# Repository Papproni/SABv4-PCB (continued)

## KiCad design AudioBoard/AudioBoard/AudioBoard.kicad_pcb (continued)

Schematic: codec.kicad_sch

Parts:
C57, C79: 100nF; C_0603_1608Metric; JLCPCB C14663
C58: 100uF tantal; CP_EIA-3528-21_Kemet-B; JLCPCB C16133
C67: 33nF; C_0805_2012Metric_Pad1.18x1.45mm_HandSolder; JLCPCB C21117
C68, C228: 1nF; C_0603_1608Metric; JLCPCB C1588
C80: 10uF tantal; CP_EIA-3216-18_Kemet-A; JLCPCB C7171
R45: 3k; R_0603_1608Metric; JLCPCB C4211
U1: LQFP-64_10x10mm_P0.5mm; JLCPCB C2913556

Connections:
+3.3V: U1.14 (PD/RST)
/HeadphoneAmplifier1/IN_N: U1.13 (OR4N); also elsewhere on the board
/HeadphoneAmplifier1/IN_P: U1.12 (OR4P); also elsewhere on the board
/HeadphoneAmplifier/IN_N: U1.11 (OL4N); also elsewhere on the board
/HeadphoneAmplifier/IN_P: U1.10 (OL4P); also elsewhere on the board
/Instrument_Input/OUT_N: U1.54 (ADC1LN); also elsewhere on the board
/Instrument_Input/OUT_P: U1.53 (ADC1LP); also elsewhere on the board
/Instrument_L1_return/OUT_N: U1.58 (ADC2LN); also elsewhere on the board
/Instrument_L1_return/OUT_P: U1.57 (ADC2LP); also elsewhere on the board
/Instrument_L1_send/IN_N: U1.40 (OL2P); also elsewhere on the board
/Instrument_L1_send/IN_P: U1.41 (OL2N); also elsewhere on the board
/Instrument_L2_return/OUT_N: U1.60 (ADC2RN); also elsewhere on the board
/Instrument_L2_return/OUT_P: U1.59 (ADC2RP); also elsewhere on the board
/Instrument_L2_send/IN_N: U1.42 (OR2P); also elsewhere on the board
/Instrument_L2_send/IN_P: U1.43 (OR2N); also elsewhere on the board
/Instrument_output_L/IN_N: U1.36 (OL1P); also elsewhere on the board
/Instrument_output_L/IN_P: U1.37 (OL1N); also elsewhere on the board
/Instrument_output_R/IN_N: U1.38 (OR1P); also elsewhere on the board
/Instrument_output_R/IN_P: U1.39 (OR1N); also elsewhere on the board
/MIC_preamp/OUT_N: U1.56 (ADC1RN); also elsewhere on the board
/MIC_preamp/OUT_P: U1.55 (ADC1RP); also elsewhere on the board
/XLR_output_L/IN_N_N: U1.9 (OR3N); also elsewhere on the board
/XLR_output_L/IN_N_P: U1.8 (OR3P); also elsewhere on the board
/XLR_output_R/IN_N_N: U1.7 (OL3N); also elsewhere on the board
/XLR_output_R/IN_N_P: U1.6 (OL3P); also elsewhere on the board
/codec/I2S.CLK: U1.21 (DBCLK), U1.28 (ABCLK)
/codec/I2S.SDI: U1.27 (ASDATA1)
/codec/I2S.SDO: U1.20 (DSDATA1)
/codec/I2S.WS: U1.22 (DLRCLK), U1.29 (ALRCLK)
/codec/SPI.CLK: U1.34 (CCLK)
/codec/SPI.CS: U1.35 (CLATCH)
/codec/SPI.MISO: U1.31 (COUT)
/codec/SPI.MOSI: U1.30 (CIN)
AD1939_FILTR: C79.2, C80.1, U1.47 (FILTR)
AD1939_LF: C67.2, C68.2, C228.2, U1.61 (LF)
AD1939_MCLKI: U1.2 (MCLKI/XI)
AD1939_MCLKO: U1.3 (MCLKO/XO)
AVDD: C68.1, C228.1, R45.2, U1.5 (AVDD), U1.45 (AVDD), U1.51 (AVDD), U1.62 (AVDD); also elsewhere on the board
DVDD: U1.17 (DVDD), U1.32 (DVDD); also elsewhere on the board
GND: C57.1, C58.2, C79.1, C80.2, U1.1 (AGND), U1.4 (AGND), U1.16 (DGND), U1.23 (VSUPPLY), U1.24 (VSENSE), U1.25 (VDRIVE), U1.33 (DGND), U1.44 (AGND), U1.46 (AGND), U1.48 (AGND); also elsewhere on the board
unnamed: C67.1, R45.1
VBIAS: C57.2, C58.1, U1.52 (CM); also elsewhere on the board

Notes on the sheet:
CM pin filter (can be used for BIAS)
FILTR filtering
MCLK is powered from external quarc osc
PLL Filters

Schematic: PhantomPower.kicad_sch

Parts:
SW2: SW_SPDT_321; SS-12D28G7; jlcpcbpart C2884748

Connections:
/power/PhantomPower/PP_EN_I: SW2.1 (C)
GND: SW2.3 (A); also elsewhere on the board
Phantom_PWR: SW2.2 (B); also elsewhere on the board

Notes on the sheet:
Must Do: - 10mA current limiter - Voltage of 24 or 48 Low noise

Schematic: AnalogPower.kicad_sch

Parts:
C88, C89, C97, C98: 100n; C_0402_1005Metric; JLCPCB C1591
C90: 33nF; C_0805_2012Metric_Pad1.18x1.45mm_HandSolder; JLCPCB C21117
C91, C92, C93, C94, C95, C96, C106, C140: 10uF; C_0402_1005Metric; JLCPCB C440198
C103, C104, C105, C107, C138, C139: 100uF; CP_Elec_5x5.4; JLCPCB C48970701
FL1, FL2: ACT3225R510-W2; L_CommonModeChoke_Coilank_ACM3225; JLCPCB C49420293
R1: 39k; R_0603_1608Metric; JLCPCB C23153
R2: 51k; R_0603_1608Metric; JLCPCB C23196
R3: 100k; R_0402_1005Metric; JLCPCB C25741
R7, R25: 10k; R_0603_1608Metric; JLCPCB C4184
R27, R34, R35, R43: 0R; R_0603_1608Metric_Pad0.98x0.95mm_HandSolder; JLCPCB C21189; not fitted
U21: TPS7A39; Texas_S-PVSON-N10_ThermalVias; JLCPCB C2685819
U22: URA2415S-6WR3; Converter_DCDC_TRACO_TEC2-12xxWI_24xxWI_48xxWI_THT; JLCPCB C21714378

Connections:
/power/AnalogPower/+15V: FL1.1, R34.1, U22.6 (+Vout)
/power/AnalogPower/+15V_FLT: C95.2, C96.2, C98.2, FL1.2, R34.2, U21.1 (INP), U21.2 (EN)
/power/AnalogPower/-15V: FL1.4, R27.1, U22.8 (-Vout)
/power/AnalogPower/-15V_FLT: C93.2, C94.2, C97.2, FL1.3, R27.2, U21.5 (INN)
/power/AnalogPower/EN: U22.3 (OnOff); also elsewhere on the board
/power/AnalogPower/VIN: C103.1, C104.1, C105.1, C106.2, FL2.1, R35.1; also elsewhere on the board
/power/AnalogPower/VIN_FLT_PMIN: C107.1, C138.1, C139.1, C140.2, FL2.2, R35.2, U22.2 (+Vin)
GND: C90.2, C91.1, C92.1, C93.1, C94.1, C95.1, C96.1, C97.1, C98.1, R7.2, U21.4 (GND), U21.11 (GND), U22.7 (Common); also elsewhere on the board
GNDPWR: C103.2, C104.2, C105.2, C106.1, FL2.4, R43.1; also elsewhere on the board
unnamed: R1.2, R2.1
unnamed: R25.1, U21.8 (BUF)
unnamed: C89.2, R3.1, R25.2, U21.7 (FBN)
unnamed: C88.1, R2.2, R7.1, U21.9 (FBP)
unnamed: C90.1, U21.3 (NR/SS)
unnamed: C107.2, C138.2, C139.2, C140.1, FL2.3, R43.2, U22.1 (-Vin)
VDD: C88.2, C91.2, R1.1, U21.10 (OUTP); also elsewhere on the board
VSS: C89.1, C92.2, R3.2, U21.6 (OUTN); also elsewhere on the board

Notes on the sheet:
Note: Filter can be bypassed if oscilaltions are visible

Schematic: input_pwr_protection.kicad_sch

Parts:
C56: 1uF; C_0603_1608Metric; JLCPCB C15849
C61: 2200uF; C_Radial_D16.0mm_H25.0mm_P7.50mm; lcscpart C2763
C141: 4.7uF; C_1206_3216Metric; JLCPCB C29823
R47: 5.6k; R_0603_1608Metric; JLCPCB C23189
R48: 30k; R_0805_2012Metric; JLCPCB C17621
R49: 100k; R_0402_1005Metric; JLCPCB C25741
R50: 20k; R_0603_1608Metric; JLCPCB C4184
R51: 0R; R_0603_1608Metric_Pad0.98x0.95mm_HandSolder; JLCPCB C21189; not fitted
R55: 0R; R_0603_1608Metric_Pad0.98x0.95mm_HandSolder; JLCPCB C21189
U3: TPS26600PWP; HTSSOP-16-1EP_4.4x5mm_P0.65mm_EP3.4x5mm_Mask2.66x2.46mm_The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; JLCPCB C544399

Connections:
/power/AnalogPower/EN: R55.2; also elsewhere on the board
/power/AnalogPower/VIN: C61.1, R49.1, R51.2, U3.15 (OUT), U3.16 (OUT); also elsewhere on the board
/power/input_pwr_protection/VIN: C56.1, R51.1, U3.1 (IN), U3.2 (IN); also elsewhere on the board
/power/input_pwr_protection/\SHDN: U3.7 (~SHDN); also elsewhere on the board
GNDPWR: C56.2, C61.2, R50.2, U3.9 (GND); also elsewhere on the board
unnamed: R47.1, U3.11 (ILIM)
unnamed: R48.1, U3.10 (IMON)
unnamed: C141.2, R47.2, R48.2, U3.3 (UVLO), U3.5 (OVP), U3.6 (MODE), U3.8 (RTN), U3.17 (RTN)
unnamed: C141.1, U3.12 (dVdT)
unnamed: R49.2, R50.1, R55.1, U3.14 (~FLT)

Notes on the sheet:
Vmonmax = 5V Rmon = Vmonmax / ( Ilim * 75*10e-6 ) Rmon = 30k Ilim = 12/Rilim = 2.14A Startup time = 1s EQ2: Tstartup/8000/VIN = Cdvdt_ideal = 5.2uF Cdvdt_real = 4.7uF
Chip Bypass
\SHDN ON: >1V OFF: 0V
PGD > 2V! for DCDC modules OpenDrain VIN=15V PGD = 2.5 V VIN=30V PGD = 5 V
RTN = UVLO = OVP 15V < VIN < 33V

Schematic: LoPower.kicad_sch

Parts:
C62, C85, C99: 100n; C_0402_1005Metric; JLCPCB C1591
C81, C86: 10uF tantal; CP_EIA-3216-18_Kemet-A; JLCPCB C7171
C82, C83, C84, C87: 47u; CP_Radial_D6.3mm_P2.50mm; JLCPCB C45673
C100: 10uF; C_0402_1005Metric; JLCPCB C440198
C101: 2200uF; C_Radial_D16.0mm_H25.0mm_P7.50mm; lcscpart C2763
C142, C143: 100uF; CP_Elec_5x5.4; JLCPCB C48970701
FB1: GZ2012D601TF; R_0805_2012Metric; JLCPCB C1017
FB2, FB3: BLM18PG121SN1D; Fuse_0603_1608Metric; JLCPCB C14709
U12, U13: AMS1117-3.3; SOT-223-3_TabPin2; JLCPCB C6186
U24: TURB2405YMD-30WR3; Converter_DCDC_TRACO_THL30-xxxxWI_THT; LCSC Part C5441767

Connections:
+5V: C85.2, C86.1, C101.1, FB1.1, FB3.2, U13.3 (VI); also elsewhere on the board
/power/AnalogPower/EN: U24.6 (Remote); also elsewhere on the board
/power/AnalogPower/VIN: FB2.1; also elsewhere on the board
AVDD: C82.1, C83.1, C84.1, U12.2 (VO); also elsewhere on the board
DVDD: C87.1, U13.2 (VO); also elsewhere on the board
GND: C62.1, C81.2, C82.2, C83.2, C84.2, C85.1, C86.2, C87.2, C99.1, C100.1, C101.2, U12.1 (GND), U13.1 (GND), U24.5 (-Vout); also elsewhere on the board
GNDPWR: C142.2, C143.2, U24.2 (-Vin); also elsewhere on the board
unnamed: C62.2, C81.1, FB1.2, U12.3 (VI)
unnamed: C142.1, C143.1, FB2.2, U24.1 (+Vin)
unnamed: C99.2, C100.2, FB3.1, U24.3 (+Vout)

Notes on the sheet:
Convert +18-24V

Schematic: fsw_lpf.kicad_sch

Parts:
C149: 100n; C_0402_1005Metric; JLCPCB C1591
R104: 1k; R_0603_1608Metric; JLCPCB C21190

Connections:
/fsw_conn/8x_lpf/IN3: R104.2; also elsewhere on the board
/fsw_conn/8x_lpf/OUT3: C149.2, R104.1; also elsewhere on the board
GND: C149.1; also elsewhere on the board

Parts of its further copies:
C147, C148, C160, C161, C162, C163, C164, C165, C166, C167, C168, C169, C170, C171, C172: 100n; C_0402_1005Metric; JLCPCB C1591
R100, R103, R105, R106, R107, R108, R109, R110, R111, R112, R113, R114, R115, R116, R139: 1k; R_0603_1608Metric; JLCPCB C21190

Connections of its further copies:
/fsw_conn/8x_lpf1/IN1: R110.2; also elsewhere on the board
/fsw_conn/8x_lpf1/IN2: R111.2; also elsewhere on the board
/fsw_conn/8x_lpf1/IN3: R112.2; also elsewhere on the board
/fsw_conn/8x_lpf1/IN4: R113.2; also elsewhere on the board
/fsw_conn/8x_lpf1/IN5: R114.2; also elsewhere on the board
/fsw_conn/8x_lpf1/IN6: R115.2; also elsewhere on the board
/fsw_conn/8x_lpf1/IN7: R116.2; also elsewhere on the board
/fsw_conn/8x_lpf1/IN8: R139.2; also elsewhere on the board
/fsw_conn/8x_lpf1/OUT1: C165.2, R110.1; also elsewhere on the board
/fsw_conn/8x_lpf1/OUT2: C166.2, R111.1; also elsewhere on the board
/fsw_conn/8x_lpf1/OUT3: C167.2, R112.1; also elsewhere on the board
/fsw_conn/8x_lpf1/OUT4: C168.2, R113.1; also elsewhere on the board
/fsw_conn/8x_lpf1/OUT5: C169.2, R114.1; also elsewhere on the board
/fsw_conn/8x_lpf1/OUT6: C170.2, R115.1; also elsewhere on the board
/fsw_conn/8x_lpf1/OUT7: C171.2, R116.1; also elsewhere on the board
/fsw_conn/8x_lpf1/OUT8: C172.2, R139.1; also elsewhere on the board
/fsw_conn/8x_lpf/IN1: R100.2; also elsewhere on the board
/fsw_conn/8x_lpf/IN2: R103.2; also elsewhere on the board
/fsw_conn/8x_lpf/IN4: R105.2; also elsewhere on the board
/fsw_conn/8x_lpf/IN5: R106.2; also elsewhere on the board
/fsw_conn/8x_lpf/IN6: R107.2; also elsewhere on the board
/fsw_conn/8x_lpf/IN7: R108.2; also elsewhere on the board
/fsw_conn/8x_lpf/IN8: R109.2; also elsewhere on the board
/fsw_conn/8x_lpf/OUT1: C147.2, R100.1; also elsewhere on the board
/fsw_conn/8x_lpf/OUT2: C148.2, R103.1; also elsewhere on the board
/fsw_conn/8x_lpf/OUT4: C160.2, R105.1; also elsewhere on the board
/fsw_conn/8x_lpf/OUT5: C161.2, R106.1; also elsewhere on the board
/fsw_conn/8x_lpf/OUT6: C162.2, R107.1; also elsewhere on the board
/fsw_conn/8x_lpf/OUT7: C163.2, R108.1; also elsewhere on the board
/fsw_conn/8x_lpf/OUT8: C164.2, R109.1; also elsewhere on the board
GND: C147.1, C148.1, C160.1, C161.1, C162.1, C163.1, C164.1, C165.1, C166.1, C167.1, C168.1, C169.1, C170.1, C171.1, C172.1; also elsewhere on the board

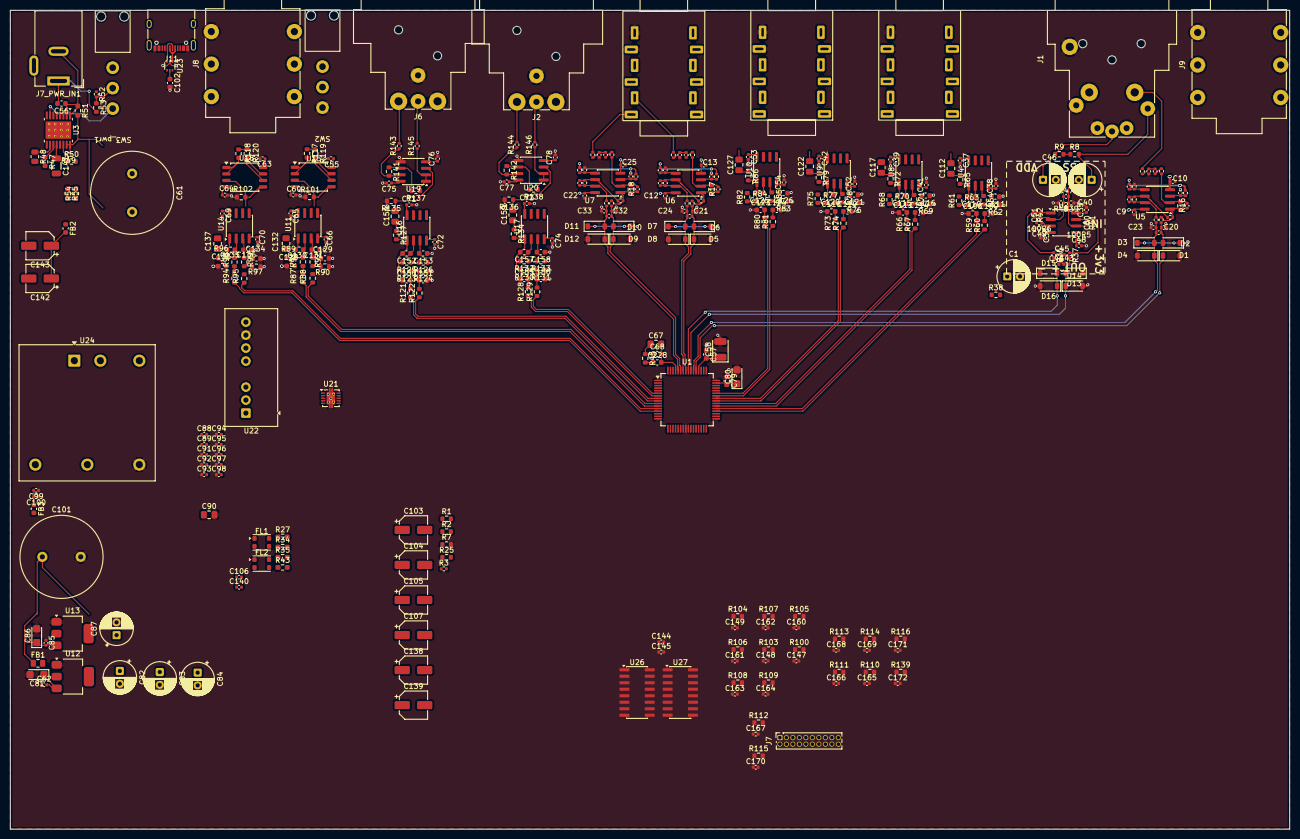
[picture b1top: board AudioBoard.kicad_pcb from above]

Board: 4 copper layers, 250.0 x 160.0 mm, 374 parts (0 on the bottom side), 210 nets.

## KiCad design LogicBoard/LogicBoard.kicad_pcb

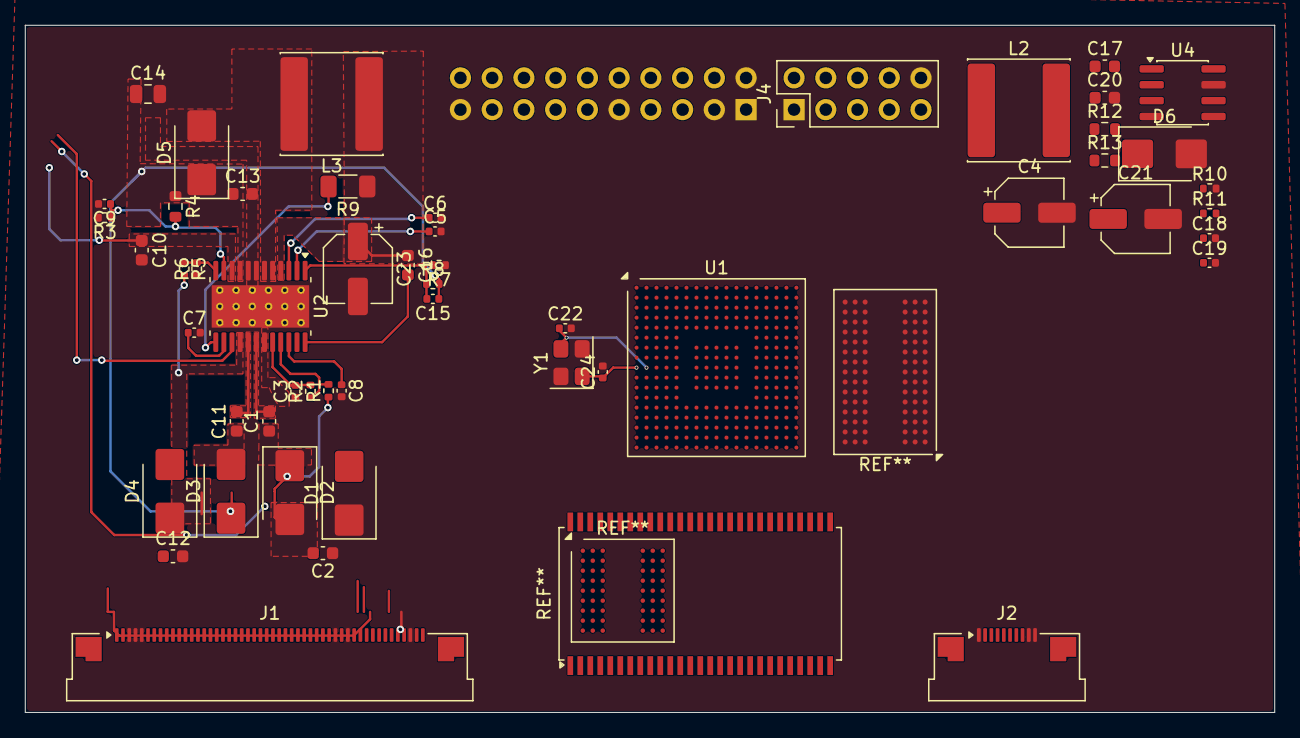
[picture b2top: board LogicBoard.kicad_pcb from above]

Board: 4 copper layers, 100.0 x 55.0 mm, 53 parts (1 on the bottom side), 36 nets.

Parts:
C1, C2, C11, C12: 330n; C_0603_1608Metric
C3: 220n; C_0402_1005Metric
C4, C23: 22u; CP_Elec_5x5.4
C5, C6: 10n; C_0402_1005Metric
C7, C15: 22p; C_0402_1005Metric
C8, C9: 2n2; C_0402_1005Metric
C10, C13: 1u; C_0603_1608Metric
C14: 22u; C_0805_2012Metric
C16, C17: 100n; C_0603_1608Metric
C18: 10p; C_0402_1005Metric
C19: 1n; C_0402_1005Metric
C20: 8.2n; C_0603_1608Metric
C21: 47u; CP_Elec_5x5.3
C22, C24: 12p; C_0402_1005Metric
D1, D2, D3, D4, D5, D6: MBRS130LT3G; D_SMB
J1: Conn_01x50; Amphenol_F32Q-1A7x1-11050_1x50-1MP_P0.5mm_Horizontal
J2: Conn_01x10; Amphenol_F32Q-1A7x1-11010_1x10-1MP_P0.5mm_Horizontal
J3: Conn_interconn; PinHeader_2x10_P2.54mm_Vertical
J4: Conn_02x5_CODEC; PinHeader_2x05_P2.54mm_Vertical
L2, L3: 3.3u; L_Changjiang_FNR8065S
R1, R8: 510k; R_0402_1005Metric
R2: 100k; R_0402_1005Metric
R3: 330k; R_0402_1005Metric
R4: 680k; R_0603_1608Metric
R5: 1Meg; R_0402_1005Metric
R6: 75k; R_0402_1005Metric
R7: 68k; R_0402_1005Metric
R9: 0R; R_1206_3216Metric_Pad1.30x1.75mm_HandSolder
R10: 3.3k; R_0402_1005Metric
R11: 10k; R_0402_1005Metric
R12: 43k; R_0603_1608Metric
R13: 390R; R_0603_1608Metric
U1: STM32H757XIHx; TFBGA-265_14x14mm_Layout17x17_P0.8mm
U2: TPS65150PWPR; HTSSOP-24-1EP_4.4x7.8mm_P0.65mm_EP3.4x7.8mm_Mask2.4x4.68mm_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
U4: TPS54331DR; SOIC-8_3.9x4.9mm_P1.27mm
Y1: X322525MOB4SI 25MHZ; Crystal_SMD_3225-4Pin_3.2x2.5mm

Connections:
/Bus_Disp_pwr.AVDD: C13.1, C14.1, C15.1, D3.1 (K), D5.1 (K), J1.1, J1.2, J1.43, R4.1, R8.2, U2.9 (SUP)
/CONN_rgb_display/Bus_Disp_pwr.DVDD: C21.1, J1.7, L2.2, R13.1
/CONN_rgb_display/Bus_Disp_pwr.VCOM: C10.1, J1.6, J1.46, U2.10 (VCOM)
/CONN_rgb_display/Bus_Disp_pwr.VGH: J1.41, U2.15 (VGH)
/CONN_rgb_display/Bus_Disp_pwr.VGL: C2.2, D2.2 (A), J1.42, R1.1
/CONN_touch_intf/+3V3: J2.7, J2.8
/PowerSection/5V: C4.1, C16.1, C23.1, J3.14, J3.16, J3.18, J3.20, L3.1, R9.1, U2.4 (VIN), U4.2 (VIN)
/PowerSection/ADJ: C7.1, U2.14 (ADJ)
/PowerSection/COMP: C8.1, U2.22 (COMP)
/PowerSection/CPI: C12.1, D4.1 (K), R5.2, U2.16 (CPI)
/PowerSection/CTRL: R9.2, U2.13 (CTRL)
/PowerSection/DLY1: C5.1, U2.2 (DLY1)
/PowerSection/DLY2: C6.1, U2.3 (DLY2)
/PowerSection/DRVN: C1.2, U2.18 (DRVN)
/PowerSection/DRVP: C11.2, U2.17 (DRVP)
/PowerSection/FB: C15.2, R7.2, R8.1, U2.1 (FB)
/PowerSection/FBN: R1.2, R2.1, U2.21 (FBN)
/PowerSection/FBP: R5.1, R6.2, U2.12 (FBP)
/PowerSection/IN: C9.1, R3.1, R4.2, U2.11 (IN)
/PowerSection/REF: C3.2, R2.2, U2.20 (REF)
/PowerSection/SW: D5.2 (A), L3.2, U2.5 (SW), U2.6 (SW)
/mcu/OSC_IN: C22.1, U1.J2 (PH0), Y1.3
/mcu/OSC_OUT: C24.1, U1.J1 (PH1), Y1.1
GND: C2.1, C3.1, C4.2, C5.2, C6.2, C7.2, C8.2, C9.2, C10.2, C12.2, C13.2, C14.2, C18.2, C19.2, C20.2, C21.2, C22.2, C23.2, C24.2, D1.1 (K), D6.2 (A), J1.3, J1.4, J1.5, J1.36, J1.38, J1.48, J2.1, J2.9, J2.10, J3.1, J3.2, J3.3, J3.9, J3.19, J4.1, J4.10, R3.2, R6.1, R7.1, R10.2, U2.7 (PGND), U2.8 (PGND), U2.19 (GND), U2.25 (THERM), U4.7 (GND), Y1.2 (G), Y1.4 (G)
unnamed: C19.1, R12.2
unnamed: C1.1, D1.2 (A), D2.1 (K)
unnamed: C11.1, D3.2 (A), D4.2 (A)
unnamed: C17.1, D6.1 (K), L2.1, U4.8 (PH)
unnamed: R11.1, R13.2
unnamed: U1.A1 (VSS), U1.A17 (VSS), U1.B2 (VSS), U1.B6 (VSS), U1.C10 (VSS), U1.C13 (VSS), U1.C16 (VSS), U1.G7 (VSS), U1.G8 (VSS), U1.G9 (VSS), U1.G10 (VSS), U1.G11 (VSS), U1.G16 (VSS), U1.H7 (VSS), U1.H8 (VSS), U1.H9 (VSS), U1.H10 (VSS), U1.H11 (VSS), U1.J3 (VSS), U1.J7 (VSS), U1.J8 (VSS), U1.J9 (VSS), U1.J10 (VSS), U1.J11 (VSS), U1.J16 (VSS), U1.J17 (VSS), U1.K7 (VSS), U1.K8 (VSS), U1.K9 (VSS), U1.K10 (VSS), U1.K11 (VSS), U1.L7 (VSS), U1.L8 (VSS), U1.L9 (VSS), U1.L10 (VSS), U1.L11 (VSS), U1.N16 (VSS), U1.R4 (VSS), U1.R8 (VSS), U1.T12 (VSS), U1.U1 (VSS), U1.U17 (VSS)
unnamed: U1.K15 (VSSDSI), U1.L15 (VSSDSI), U1.M15 (VSSDSI)
unnamed: C16.2, U2.24 (FDLY)
unnamed: C17.2, U4.1 (BOOT)
unnamed: C18.1, R12.1, U4.6 (COMP)
unnamed: C20.1, U4.4 (SS)
unnamed: R10.1, R11.2, U4.5 (VSENSE)

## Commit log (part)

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2026-05-09 Create .gitignore for KiCad project
    Add a .gitignore file for KiCad project files and temporary files.
2026-05-09 Created kicad project for logic board
    -added hierarchy
    -added lcd driver circuit
2026-05-16 added jlcpcb nums to some parts
2026-05-17 lcd schematic now matches requirement, added 3v3 dcdc stage for MCUs
2026-05-17 Created display psu layout
2026-05-27 experimenting with bga
2026-05-27 Created kicad project
2026-05-28 added input section
2026-05-30 input section with templates are working
2026-05-30 Created input sections
2026-05-30 added microphone preamp
2026-05-30 added xlr output stage
2026-05-31 xlr frontends added
2026-06-02 added dxf file to pcb view
2026-06-14 added jack IO, headphone amp cirucit
2026-06-15 added pwr sw and headphone out
2026-06-15 added connectors to pcb
2026-06-23 added lcscpart to components and assigned footprints
